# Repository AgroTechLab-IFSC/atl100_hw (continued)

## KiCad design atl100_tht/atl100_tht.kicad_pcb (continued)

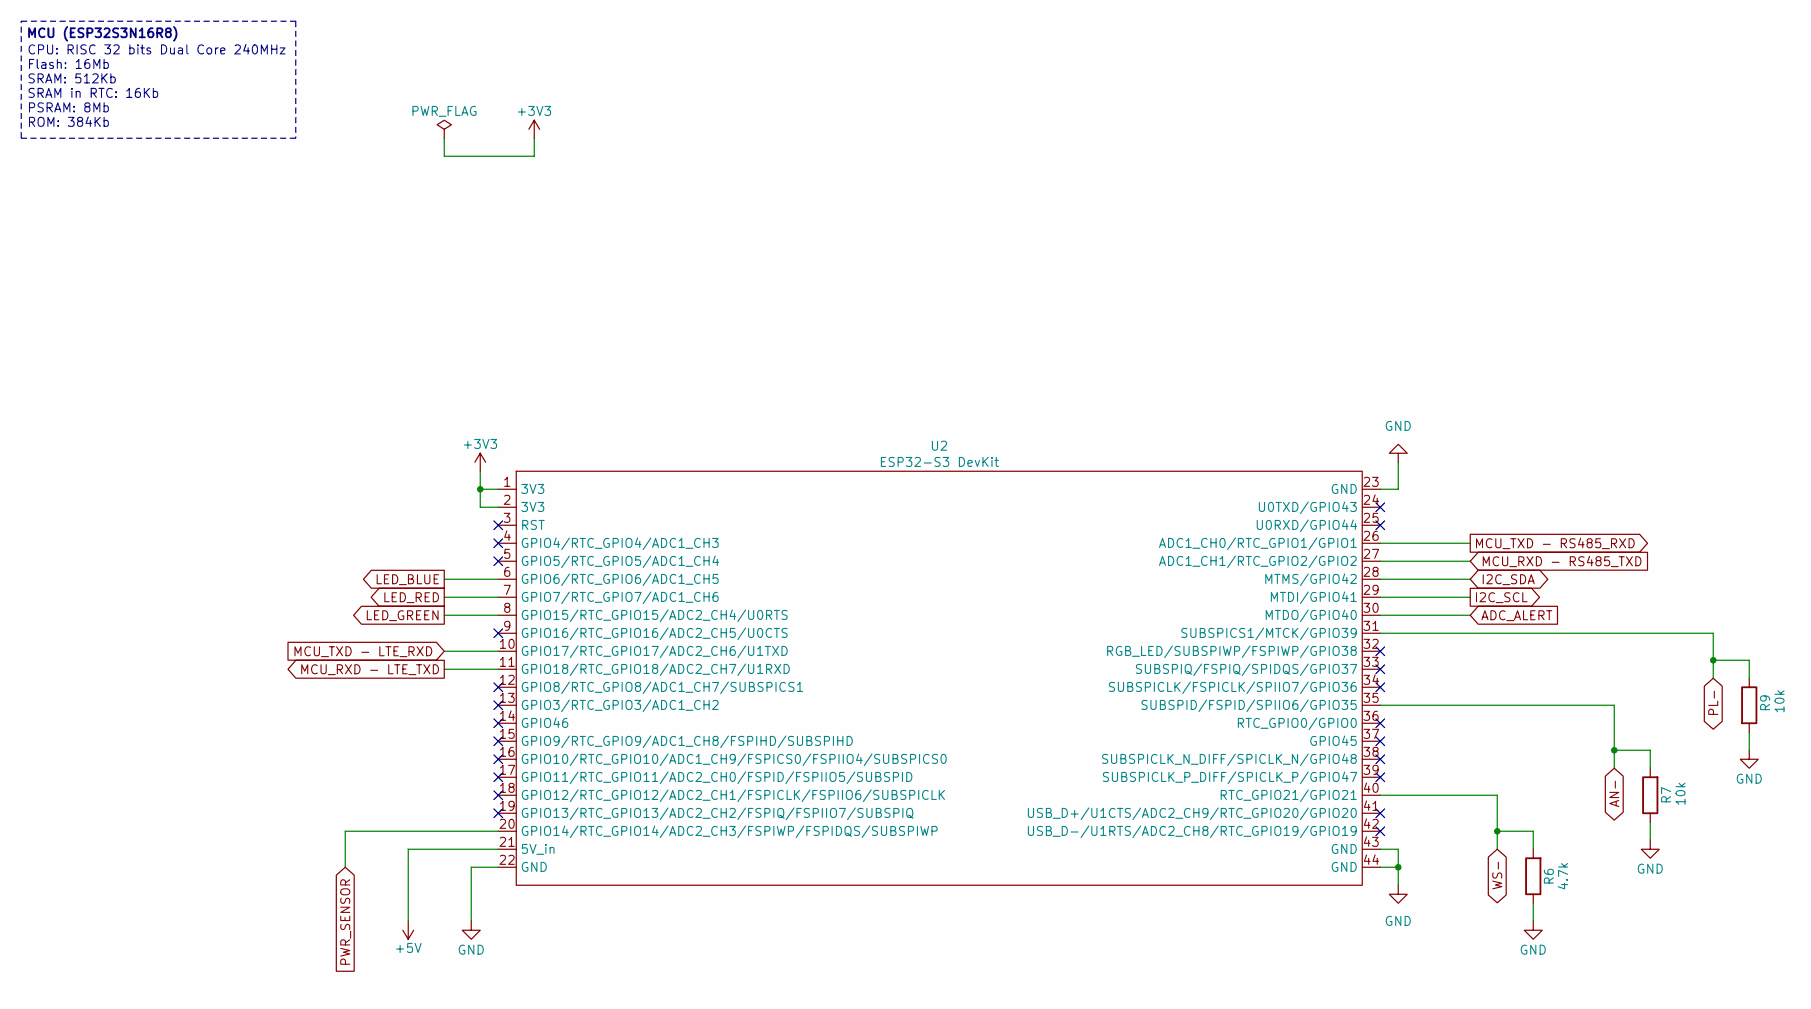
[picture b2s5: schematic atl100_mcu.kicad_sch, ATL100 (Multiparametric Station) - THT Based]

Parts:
R6: 4.7k; R_Axial_DIN0207_L6.3mm_D2.5mm_P10.16mm_Horizontal; Part Number Std
R7, R9: 10k; R_Axial_DIN0207_L6.3mm_D2.5mm_P10.16mm_Horizontal; Part Number Std
U2: ESP32-S3 DevKit; ESP32S3N16R8_DevKit; Part Number AI-S3

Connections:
+3V3: U2.1 (3V3), U2.2 (3V3); also elsewhere on the board
+5V: U2.21 (5V_in); also elsewhere on the board
ADC_ALERT: U2.30 (MTDO/GPIO40); also elsewhere on the board
AN-: R7.2, U2.35 (SUBSPID/FSPID/SPIIO6/GPIO35); also elsewhere on the board
GND: R6.1, R7.1, R9.2, U2.22 (GND), U2.23 (GND), U2.43 (GND), U2.44 (GND); also elsewhere on the board
I2C_SCL: U2.29 (MTDI/GPIO41); also elsewhere on the board
I2C_SDA: U2.28 (MTMS/GPIO42); also elsewhere on the board
LED_BLUE: U2.6 (GPIO6/RTC_GPIO6/ADC1_CH5); also elsewhere on the board
LED_GREEN: U2.8 (GPIO15/RTC_GPIO15/ADC2_CH4/U0RTS); also elsewhere on the board
LED_RED: U2.7 (GPIO7/RTC_GPIO7/ADC1_CH6); also elsewhere on the board
MCU_RXD - LTE_TXD: U2.11 (GPIO18/RTC_GPIO18/ADC2_CH7/U1RXD); also elsewhere on the board
MCU_RXD - RS485_TXD: U2.27 (ADC1_CH1/RTC_GPIO2/GPIO2); also elsewhere on the board
MCU_TXD - LTE_RXD: U2.10 (GPIO17/RTC_GPIO17/ADC2_CH6/U1TXD); also elsewhere on the board
MCU_TXD - RS485_RXD: U2.26 (ADC1_CH0/RTC_GPIO1/GPIO1); also elsewhere on the board
PL-: R9.1, U2.31 (SUBSPICS1/MTCK/GPIO39); also elsewhere on the board
PWR_SENSOR: U2.20 (GPIO14/RTC_GPIO14/ADC2_CH3/FSPIWP/FSPID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); also elsewhere on the board
WS-: R6.2, U2.40 (RTC_GPIO21/GPIO21); also elsewhere on the board

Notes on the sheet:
CPU: RISC 32 bits Dual Core 240MHz Flash: 16Mb SRAM: 512Kb SRAM in RTC: 16Kb PSRAM: 8Mb ROM: 384Kb
MCU (ESP32S3N16R8)

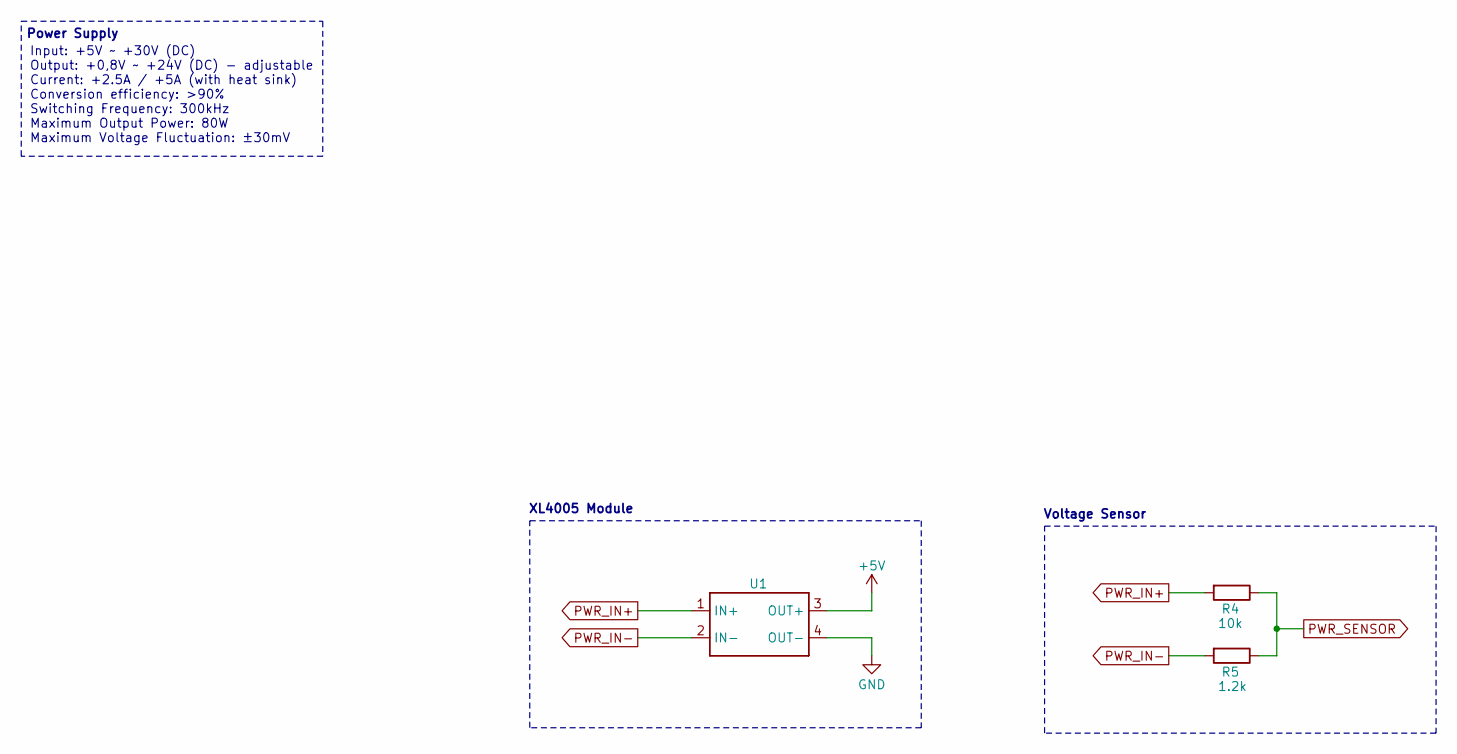
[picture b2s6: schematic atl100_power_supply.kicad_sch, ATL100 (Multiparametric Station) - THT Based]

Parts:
R4: 10k; R_Axial_DIN0207_L6.3mm_D2.5mm_P10.16mm_Horizontal; Part Number Std
R5: 1.2k; R_Axial_DIN0207_L6.3mm_D2.5mm_P10.16mm_Horizontal; Part Number Std
U1: XL4005_Module; Part Number XL4005

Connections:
+5V: U1.3 (OUT+); also elsewhere on the board
GND: U1.4 (OUT-); also elsewhere on the board
PWR_IN+: R4.2, U1.1 (IN+); also elsewhere on the board
PWR_IN-: R5.2, U1.2 (IN-); also elsewhere on the board
PWR_SENSOR: R4.1, R5.1; also elsewhere on the board

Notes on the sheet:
Voltage Sensor
XL4005 Module
Input: +5V ~ +30V (DC) Output: +0,8V ~ +24V (DC) - adjustable Current: +2.5A / +5A (with heat sink) Conversion efficiency: >90% Switching Frequency: 300kHz Maximum Output Power: 80W Maximum Voltage Fluctuation: ±30mV
Power Supply

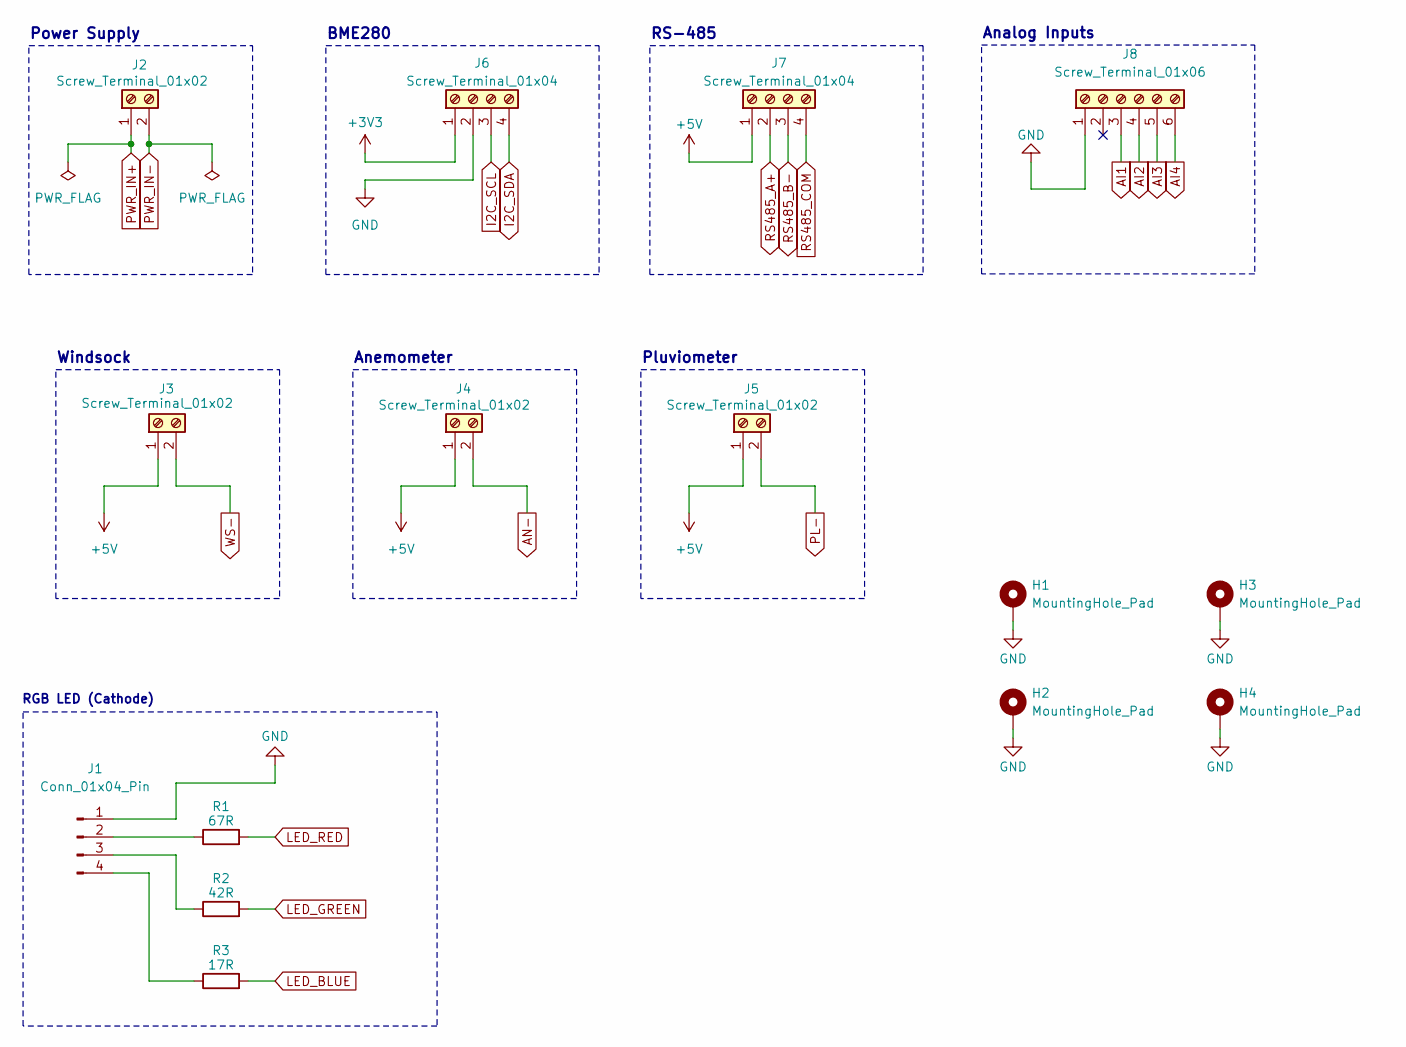
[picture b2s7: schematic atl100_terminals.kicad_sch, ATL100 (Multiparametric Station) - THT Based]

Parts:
H1, H2, H3, H4: MountingHole_Pad; MountingHole_2.2mm_M2_Pad_Via
J1: Conn_01x04_Pin; PinHeader_1x04_P2.54mm_Vertical; Part Number Std
J2, J3, J4, J5: Screw_Terminal_01x02; TerminalBlock_Phoenix_MKDS-1,5-2-5.08_1x02_P5.08mm_Horizont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; Part Number Std
J6, J7: Screw_Terminal_01x04; TerminalBlock_Phoenix_MKDS-1,5-4-5.08_1x04_P5.08mm_Horizont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; Part Number Std
J8: Screw_Terminal_01x06; TerminalBlock_Phoenix_MKDS-1,5-6-5.08_1x06_P5.08mm_Horizont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; Part Number Std
R1: 67R; R_Axial_DIN0207_L6.3mm_D2.5mm_P10.16mm_Horizontal; Part Number Std
R2: 42R; R_Axial_DIN0207_L6.3mm_D2.5mm_P10.16mm_Horizontal; Part Number Std
R3: 17R; R_Axial_DIN0207_L6.3mm_D2.5mm_P10.16mm_Horizontal; Part Number Std

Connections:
+3V3: J6.1; also elsewhere on the board
+5V: J3.1, J4.1, J5.1, J7.1; also elsewhere on the board
AI1: J8.3; also elsewhere on the board
AI2: J8.4; also elsewhere on the board
AI3: J8.5; also elsewhere on the board
AI4: J8.6; also elsewhere on the board
AN-: J4.2; also elsewhere on the board
GND: H1.1, H2.1, H3.1, H4.1, J1.1, J6.2, J8.1; also elsewhere on the board
I2C_SCL: J6.3; also elsewhere on the board
I2C_SDA: J6.4; also elsewhere on the board
LED_BLUE: R3.2; also elsewhere on the board
LED_GREEN: R2.2; also elsewhere on the board
LED_RED: R1.2; also elsewhere on the board
unnamed: J1.2, R1.1
unnamed: J1.3, R2.1
unnamed: J1.4, R3.1
PL-: J5.2; also elsewhere on the board
PWR_IN+: J2.1; also elsewhere on the board
PWR_IN-: J2.2; also elsewhere on the board
RS485_A+: J7.2; also elsewhere on the board
RS485_B-: J7.3; also elsewhere on the board
RS485_COM: J7.4; also elsewhere on the board
WS-: J3.2; also elsewhere on the board

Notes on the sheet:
Anemometer
Windsock
Pluviometer
Analog Inputs
Power Supply
BME280
RS-485
RGB LED (Cathode)

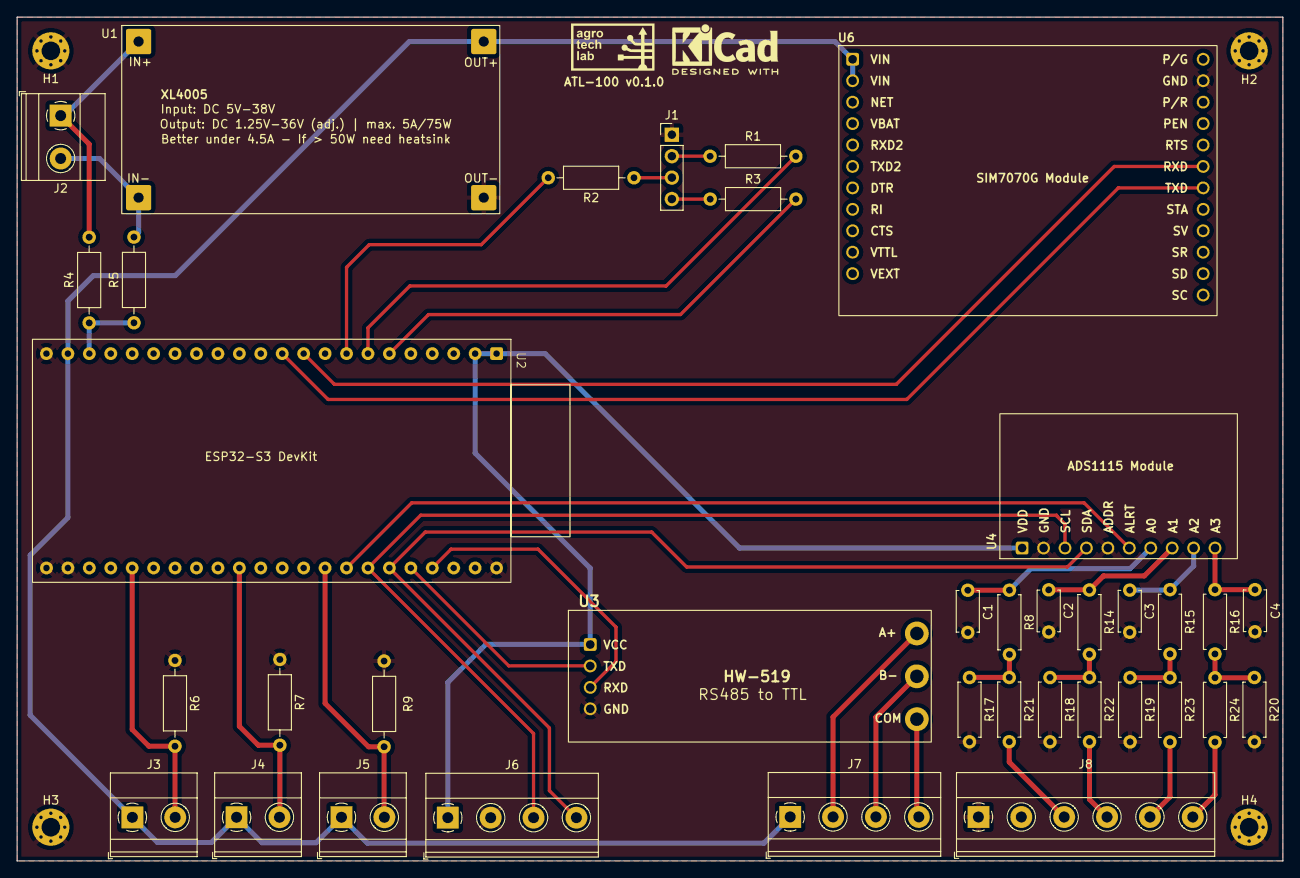
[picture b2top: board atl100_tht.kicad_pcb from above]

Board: 2 copper layers, 150.0 x 100.0 mm, 41 parts (0 on the bottom side), 37 nets.

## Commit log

2024-07-01 feat: RS-485 #6
2024-09-06 feat: Schematic updated (v0.1.0)
2024-10-28 feat: Version 1.0.0
2024-10-30 feat: Updated pins to RS-485 UART
2025-01-14 docs: Update documentation
2025-01-14 ci: Github files updated
2025-01-14 feat: Released v0.1.0 of THT project
2025-01-14 docs: Updated readme
2025-01-14 docs: Update README.md
2025-06-01 build: Project refactory
2025-06-02 feat: Main board schematic updated
2025-06-05 feat: Updated to v0.2.0
